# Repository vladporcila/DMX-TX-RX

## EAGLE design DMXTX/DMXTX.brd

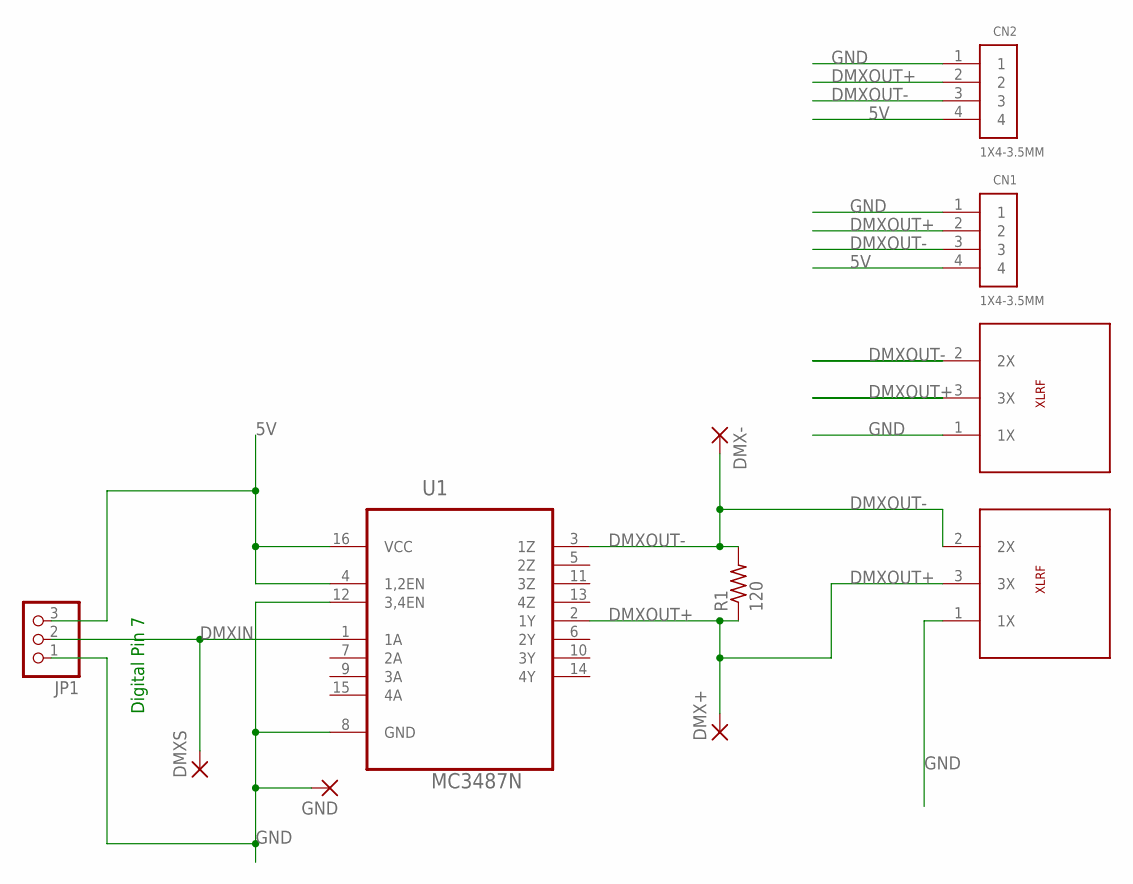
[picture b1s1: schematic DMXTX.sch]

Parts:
CN1, CN2: 1X4-3.5MM; 1X04-3.5MM
DMX+: 3,81/1,4
DMX-: 3,81/1,4
DMXS: 3,81/1,4
GND: 3,81/1,4
JP1: PINHD-1X3; 1X03
R1: 120; 0414/15
U1: MC3487N; DIP254P762X508-16
U$1, U$2: XLRCONNECTOR; DMXF3PIN

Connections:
5V: CN1.4, CN2.4, JP1.3, U1.4 (1,2EN), U1.16 (VCC)
DMXIN: DMXS.1, JP1.2, U1.1 (1A)
DMXOUT+: CN1.2, CN2.2, DMX+.1, R1.1, U1.2 (1Y), U$1.3 (3X), U$2.3 (3X)
DMXOUT-: CN1.3, CN2.3, DMX-.1, R1.2, U1.3 (1Z), U$1.2 (2X), U$2.2 (2X)
GND: CN1.1, CN2.1, GND.1, JP1.1, U1.8 (GND), U1.12 (3,4EN), U$1.1 (1X), U$2.1 (1X)

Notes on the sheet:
Digital Pin 7

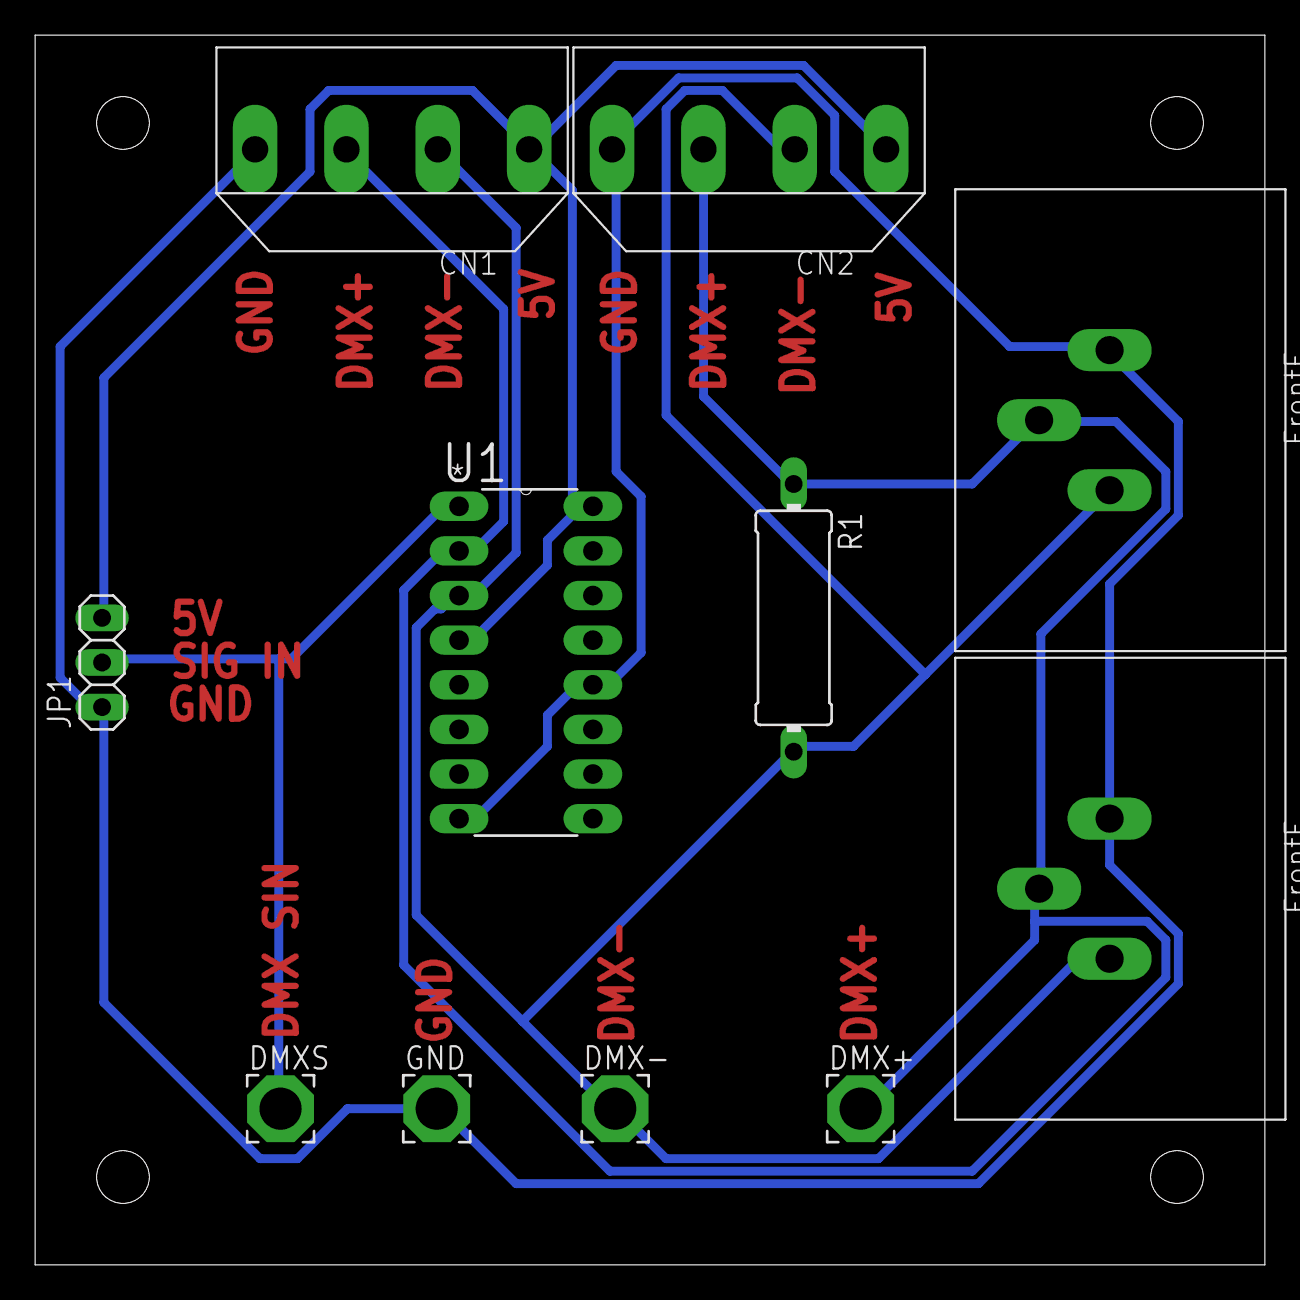
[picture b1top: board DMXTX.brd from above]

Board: 2 copper layers, 70.0 x 70.0 mm, 11 parts (0 on the bottom side), 5 nets.

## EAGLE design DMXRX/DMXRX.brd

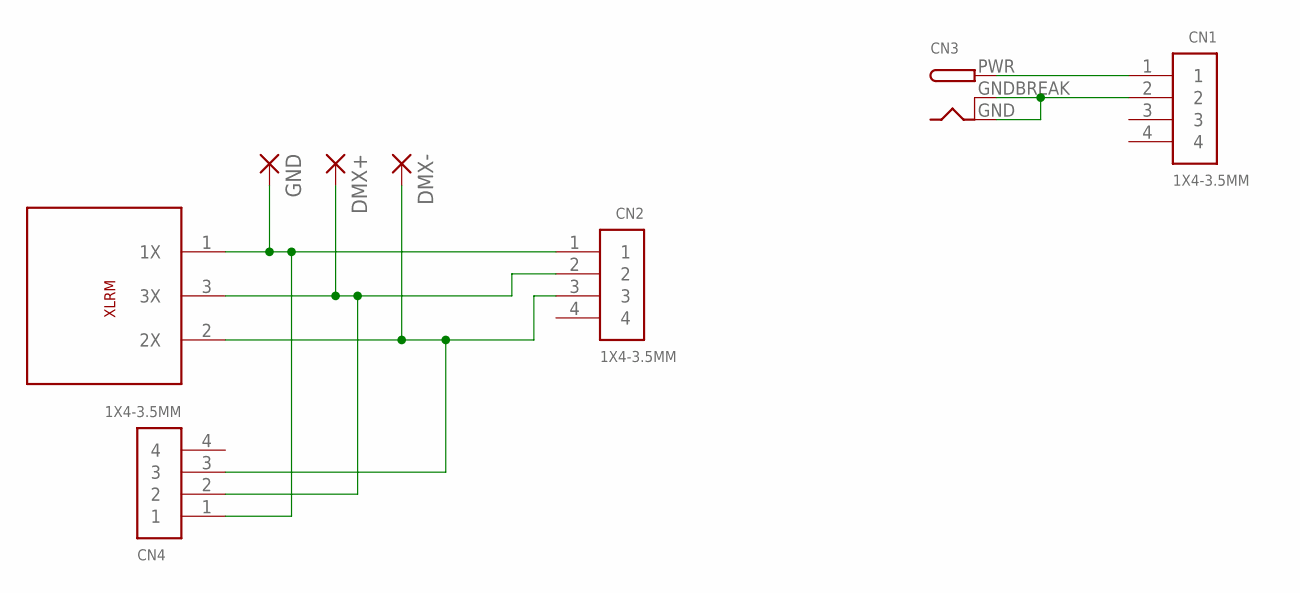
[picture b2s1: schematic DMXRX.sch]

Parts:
CN1, CN2, CN4: 1X4-3.5MM; 1X04-3.5MM
CN3: DCBARRELPTH; DCJACK_2MM_PTH
DMX+: 3,81/1,4
DMX-: 3,81/1,4
GND: 3,81/1,4
U$1: XLRCONNCTORM; DMX3PINF

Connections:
DMX+: CN2.2, CN4.2, DMX+.1, U$1.3 (3X)
DMX-: CN2.3, CN4.3, DMX-.1, U$1.2 (2X)
GND: CN2.1, CN4.1, GND.1, U$1.1 (1X)
GNDP: CN1.2, CN3.GND, CN3.GNDBREAK
PWR: CN1.1, CN3.PWR

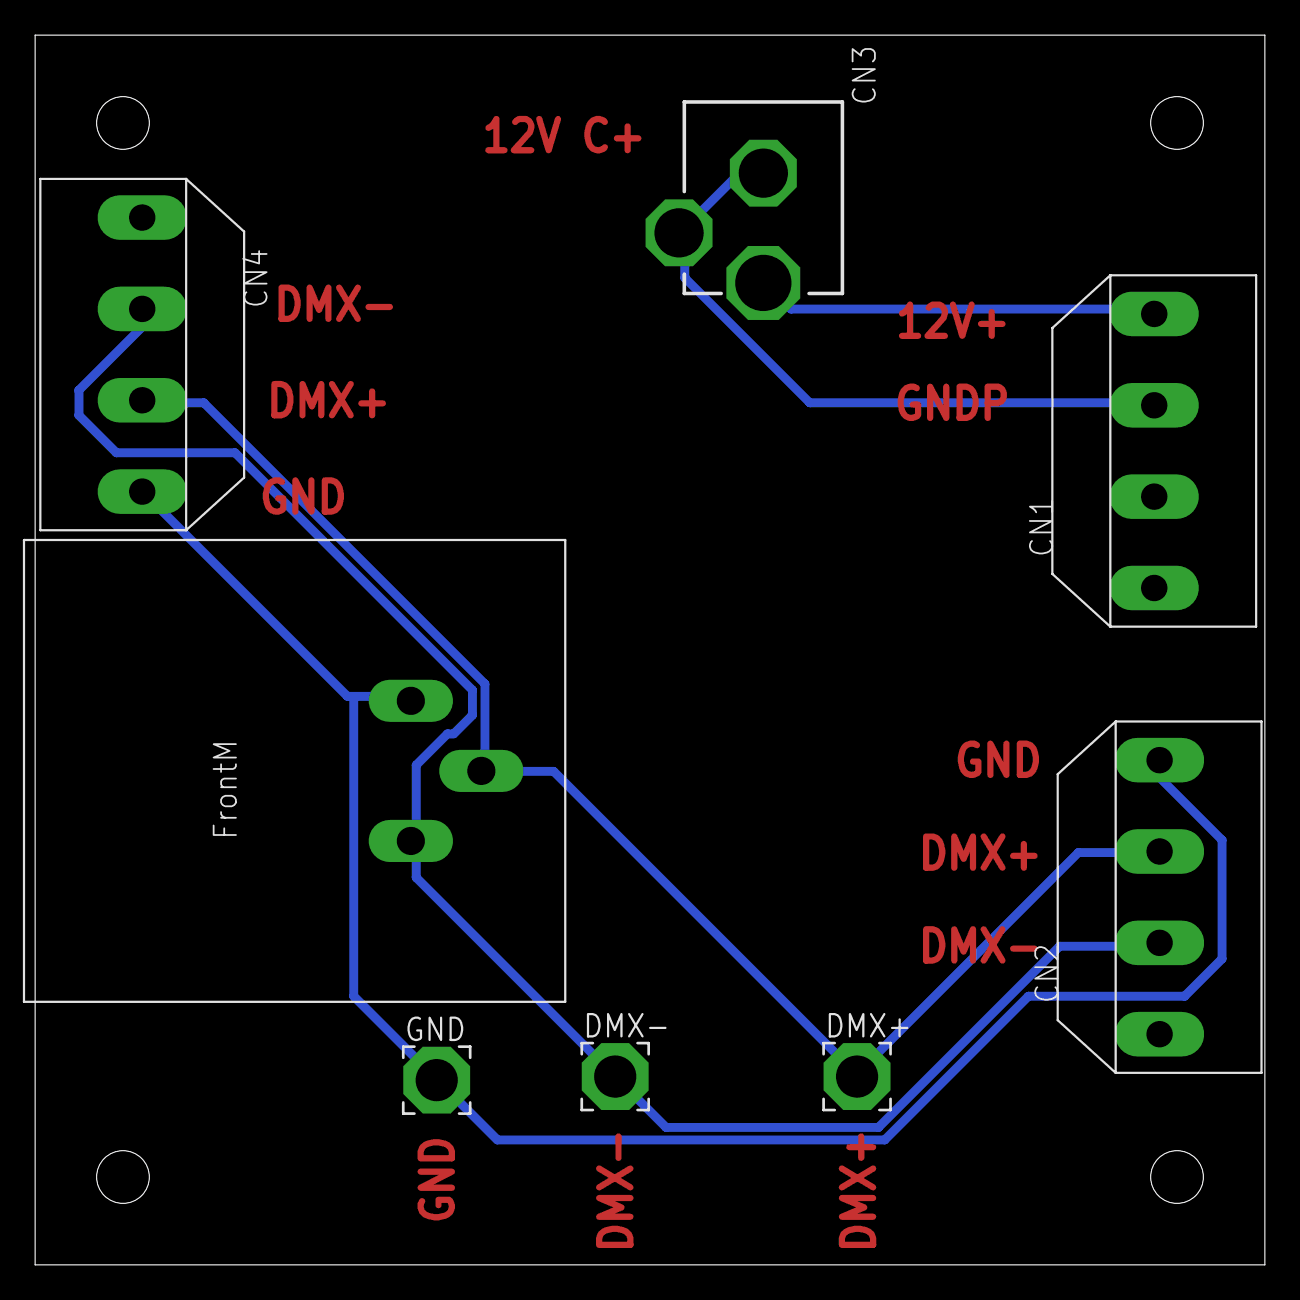
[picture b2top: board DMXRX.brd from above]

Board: 2 copper layers, 70.0 x 70.0 mm, 8 parts (0 on the bottom side), 5 nets.

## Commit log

2016-10-03 :confetti_ball: Added .gitattributes & .gitignore files
2016-10-03 DMX Serial RX TX
    DMX Serial RX TX
2016-10-03 Shield Schematic
    Shield Schematic
2016-11-23 DMX manual Reciever
    DMX manual Reciever
2016-11-24 Update
    Update
2016-12-08 DMXTestbed
    DMXTestbed
2016-12-08 Fixed Hole size
    Fixed Hole size
